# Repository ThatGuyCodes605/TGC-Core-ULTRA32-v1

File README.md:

# TGC-Core-ULTRA32-v1

## Overview
The **TGC-Core-ULTRA32-v1** is an open-source, high-performance hardware development core board based on the **ESP32** platform. Engineered for wireless application prototyping and IoT deployment, [...]

This repository contains the complete set of KiCad EDA files (version 10.0) necessary to view, modify, or manufacture the printed circuit board (PCB).

---

## Key Hardware Features

* **Microcontroller Core:** Powered by an **ESP32-WROOM-32** module, featuring a dual-core 32-bit Xtensa LX6 processor running up to 240 MHz.
* **Wireless Capabilities:** Integrated **Wi-Fi** (802.11 b/g/n) and dual-mode **Bluetooth** (Classic & BLE) with an onboard PCB trace antenna.
* **Seamless Programming:** Features an onboard **CP2102N** USB-to-UART master bridge chip, enabling effortless code flashing and hardware debugging.
* **Modern Power & Data Interface:** Equipped with a physical **USB Type-C** connector wired for high-reliability USB 2.0 configuration.
* **Onboard Power Regulation:** An onboard **AMS1117-3.3** Low Dropout (LDO) linear regulator steps down 5V VBUS power to a stable 3.3V rail capable of driving up to 1A.
* **Prototyping Breakout:** System pins and GPIO extensions are cleanly routed out to a generic single-row 19-pin hardware header (`Conn_01x19`).
* **PCB Specifications:** A robust 4-layer FR4 signal stackup engineered for optimal routing paths, power decoupling, and signal integrity.

---

## Repository Structure

The project is entirely self-contained within the following native KiCad design files:

| File Name | Description |
| :--- | :--- |
| `TGC-Core-ULTRA32-v1.kicad_pro` | The main **KiCad Project file**. Open this file to initialize the system workspace. |
| `TGC-Core-ULTRA32-v1.kicad_sch` | The **Schematic file**. Outlines the logical connections between the ESP32, CP2102N bridge, and power stages. |
| `TGC-Core-ULTRA32-v1.kicad_pcb` | The **PCB Layout file**. Houses the physical 4-layer trace configurations, via sizing, and physical board outlines. |
| `image_3c0a04.png` | A visual reference render of the completed board layout. |

---

## Getting Started

### 1. Hardware Inspection and Design
To view or modify the hardware design layout:
1. Download and install [KiCad EDA](https://www.kicad.org/) (ensure you are using KiCad v10 or newer to parse the modern project syntax).
2. Open the `TGC-Core-ULTRA32-v1.kicad_pro` file.
3. Launch the Schematic Editor or PCB Layout Editor to inspect components, footprints, and the default 4-layer layout structure.

### 2. Programming Setup
Because this core board uses standard ESP32-WROOM-32 pinouts and a CP2102N UART controller, it functions natively inside the ESP32 firmware environment:
1. Install the [Arduino IDE](https://www.arduino.cc/en/software) or configure an environment in **VS Code / PlatformIO**.
2. Add the ESP32 board package URL to your environments manager if using the Arduino IDE.
3. Connect the hardware core via a standard USB-C cable.
4. Under **Tools > Board**, select **"ESP32 Dev Module"** (or generic ESP32 WROOM module).
5. Match the assigned serial port and deploy your firmware sketches normally.

---

## License

This hardware design and its accompanying documentation are licensed under the **GNU General Public License v3.0 (GPL-3.0-or-later)**.

Summary of your rights under GPLv3:
* You are free to use, study, share, and modify the material.
* If you distribute the work (or a derivative), you must license the whole work under GPLv3 as well (share-alike).
* You must provide source for distributed derivative works and include the GPLv3 license text and copyright notices.

For the full legal text, see the GNU licenses page: https://www.gnu.org/licenses/gpl-3.0.html

Note: To make the change complete, consider adding a `LICENSE` file containing the full GPLv3 text and an explicit copyright line (for example: "Copyright (c) 2026 ThatGuyCodes605"). I can add that file for you if you want.

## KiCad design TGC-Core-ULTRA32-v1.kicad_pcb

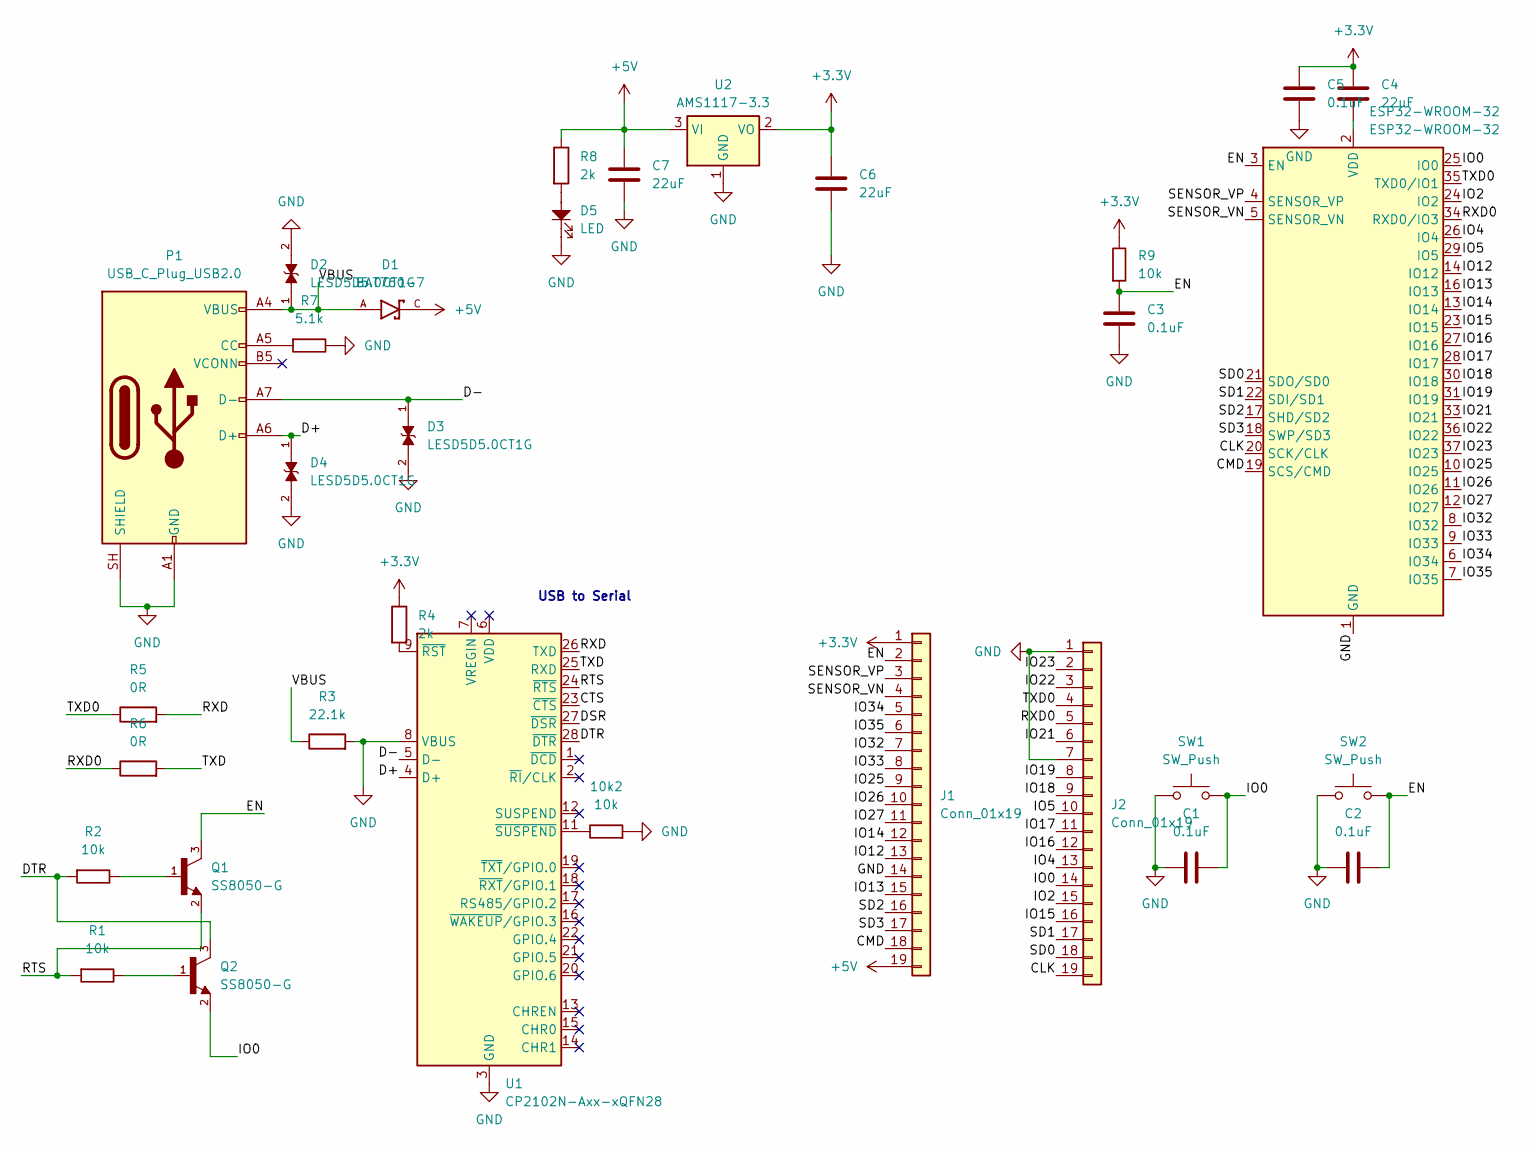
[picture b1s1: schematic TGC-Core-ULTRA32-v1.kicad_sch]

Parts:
10k2: 10k; R_0402_1005Metric
C1, C2, C3, C5: 0.1uF; C_0603_1608Metric
C4, C6, C7: 22uF; C_1206_3216Metric
D1: BAT760-7; SOD2513X120N; PARTREV 9-2
D2, D3, D4: LESD5D5.0CT1G; TVS_LESD5D5.0CT1G; PARTREV O
D5: LED; LED_0805_2012Metric
ESP32-WROOM-32: ESP32-WROOM-32
J1, J2: Conn_01x19; PinHeader_1x19_P2.54mm_Vertical
P1: USB_C_Plug_USB2.0; USB_C_Receptacle_HRO_TYPE-C-31-M-12
Q1, Q2: SS8050-G; TRANS_SS8050-G; PARTREV A
R1, R2, R9: 10k; R_0402_1005Metric
R3: 22.1k; R_0402_1005Metric
R4, R8: 2k; R_0402_1005Metric
R5, R6: 0R; R_0402_1005Metric
R7: 5.1k; R_0402_1005Metric
SW1, SW2: SW_Push; SW_SPST_SKQG_WithoutStem
U1: CP2102N-Axx-xQFN28; QFN-28-1EP_5x5mm_P0.5mm_EP3.35x3.35mm
U2: AMS1117-3.3; SOT-223-3_TabPin2

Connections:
+3.3V: C4.1, C5.1, C6.1, J1.1, R4.1, R9.2, U2.2 (VO)
+5V: C7.1, D1.C, J1.19, R8.1, U2.3 (VI)
/CLK: ESP32-WROOM-32.20 (SCK/CLK), J2.19
/CMD: ESP32-WROOM-32.19 (SCS/CMD), J1.18
/CTS: U1.23 (~CTS)
/D+: D4.1, P1.A6 (D+), U1.4 (D+)
/D-: D3.1, P1.A7 (D-), U1.5 (D-)
/DSR: U1.27 (~DSR)
/DTR: Q2.3, R2.1, U1.28 (~DTR)
/EN: C2.1, C3.1, ESP32-WROOM-32.3 (EN), J1.2, Q1.3, R9.1, SW2.2
/IO0: C1.1, ESP32-WROOM-32.25 (IO0), J2.14, Q2.2, SW1.2
/IO2: ESP32-WROOM-32.24 (IO2), J2.15
/IO4: ESP32-WROOM-32.26 (IO4), J2.13
/IO5: ESP32-WROOM-32.29 (IO5), J2.10
/IO12: ESP32-WROOM-32.14 (IO12), J1.13
/IO13: ESP32-WROOM-32.16 (IO13), J1.15
/IO14: ESP32-WROOM-32.13 (IO14), J1.12
/IO15: ESP32-WROOM-32.23 (IO15), J2.16
/IO16: ESP32-WROOM-32.27 (IO16), J2.12
/IO17: ESP32-WROOM-32.28 (IO17), J2.11
/IO18: ESP32-WROOM-32.30 (IO18), J2.9
/IO19: ESP32-WROOM-32.31 (IO19), J2.8
/IO21: ESP32-WROOM-32.33 (IO21), J2.6
/IO22: ESP32-WROOM-32.36 (IO22), J2.3
/IO23: ESP32-WROOM-32.37 (IO23), J2.2
/IO25: ESP32-WROOM-32.10 (IO25), J1.9
/IO26: ESP32-WROOM-32.11 (IO26), J1.10
/IO27: ESP32-WROOM-32.12 (IO27), J1.11
/IO32: ESP32-WROOM-32.8 (IO32), J1.7
/IO33: ESP32-WROOM-32.9 (IO33), J1.8
/IO34: ESP32-WROOM-32.6 (IO34), J1.5
/IO35: ESP32-WROOM-32.7 (IO35), J1.6
/RTS: Q1.2, R1.1, U1.24 (~RTS)
/RXD: R5.2, U1.26 (TXD)
/RXD0: ESP32-WROOM-32.34 (RXD0/IO3), J2.5, R6.1
/SD0: ESP32-WROOM-32.21 (SDO/SD0), J2.18
/SD1: ESP32-WROOM-32.22 (SDI/SD1), J2.17
/SD2: ESP32-WROOM-32.17 (SHD/SD2), J1.16
/SD3: ESP32-WROOM-32.18 (SWP/SD3), J1.17
/SENSOR_VN: ESP32-WROOM-32.5 (SENSOR_VN), J1.4
/SENSOR_VP: ESP32-WROOM-32.4 (SENSOR_VP), J1.3
/TXD: R6.2, U1.25 (RXD)
/TXD0: ESP32-WROOM-32.35 (TXD0/IO1), J2.4, R5.1
/VBUS: D1.A, D2.1, P1.A4 (VBUS), P1.A9 (VBUS), P1.B4 (VBUS), P1.B9 (VBUS), R3.1
GND: 10k2.1, C1.2, C2.2, C3.2, C5.2, C6.2, C7.2, D2.2, D3.2, D4.2, D5.1, ESP32-WROOM-32.1 (GND), ESP32-WROOM-32.15 (GND), ESP32-WROOM-32.38 (GND), ESP32-WROOM-32.39 (GND), J1.14, J2.1, J2.7, P1.A1 (GND), P1.A12 (GND), P1.B1 (GND), P1.B12 (GND), P1.SH (SHIELD), R3.2, R7.2, SW1.1, SW2.1, U1.3 (GND), U1.8 (VBUS), U1.29 (GND), U2.1 (GND); also elsewhere on the board
unnamed: D5.2, R8.2
unnamed: C4.2, ESP32-WROOM-32.2 (VDD)
unnamed: P1.A5 (CC), R7.1
unnamed: Q1.1, R2.2
unnamed: Q2.1, R1.2
unnamed: R4.2, U1.9 (~RST)
unnamed 51: 10k2.2, U1.11 (~SUSPEND); also elsewhere on the board

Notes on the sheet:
USB to Serial

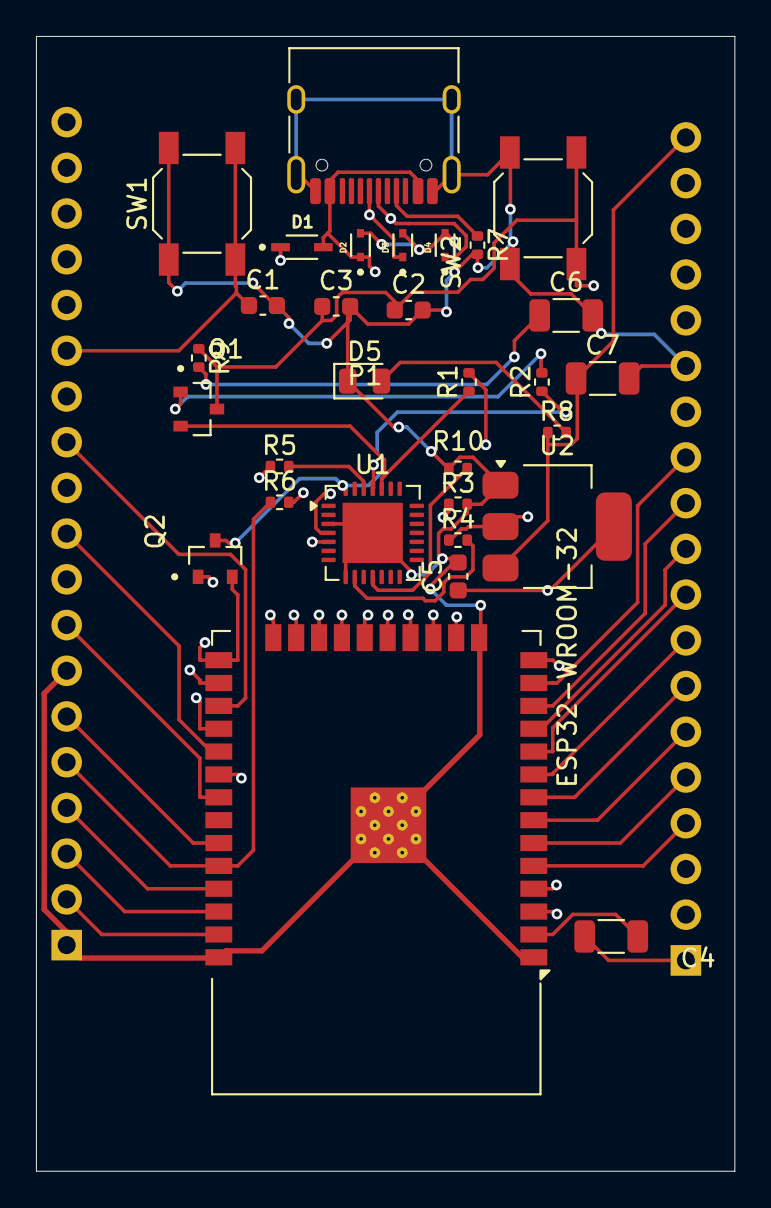
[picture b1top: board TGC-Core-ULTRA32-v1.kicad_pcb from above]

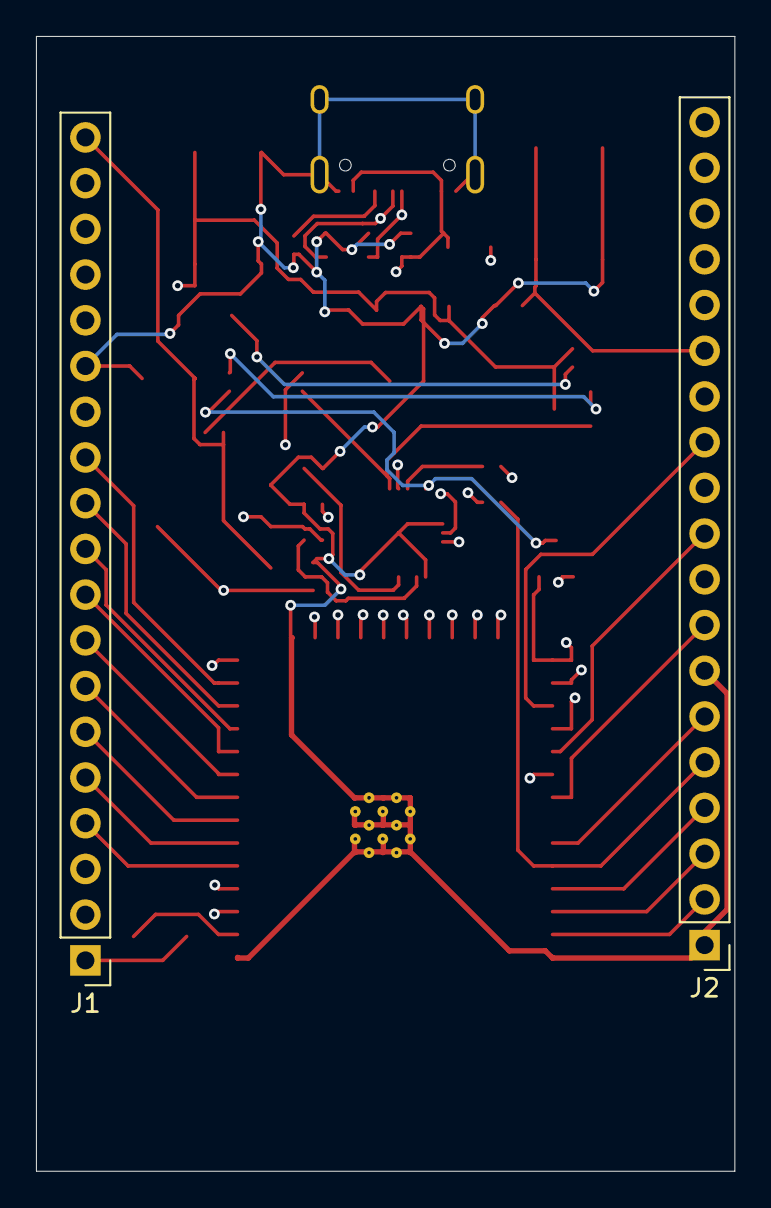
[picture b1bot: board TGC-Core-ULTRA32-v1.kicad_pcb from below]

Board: 4 copper layers, 38.8 x 63.0 mm, 32 parts (2 on the bottom side), 50 nets.

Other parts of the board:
R10: 10k; R_0402_1005Metric

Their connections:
GND: R10.1; also elsewhere on the board
unnamed 51: R10.2; also elsewhere on the board

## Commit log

2026-06-02 Enhance README with comprehensive project details
    Expanded the README to include detailed project overview, key hardware features, repository structure, getting started instructions, and licensing information.
2026-06-03 Create LICENCE
2026-06-07 Change license to GNU GPLv3 in README
2026-06-07 Create LICENSE
